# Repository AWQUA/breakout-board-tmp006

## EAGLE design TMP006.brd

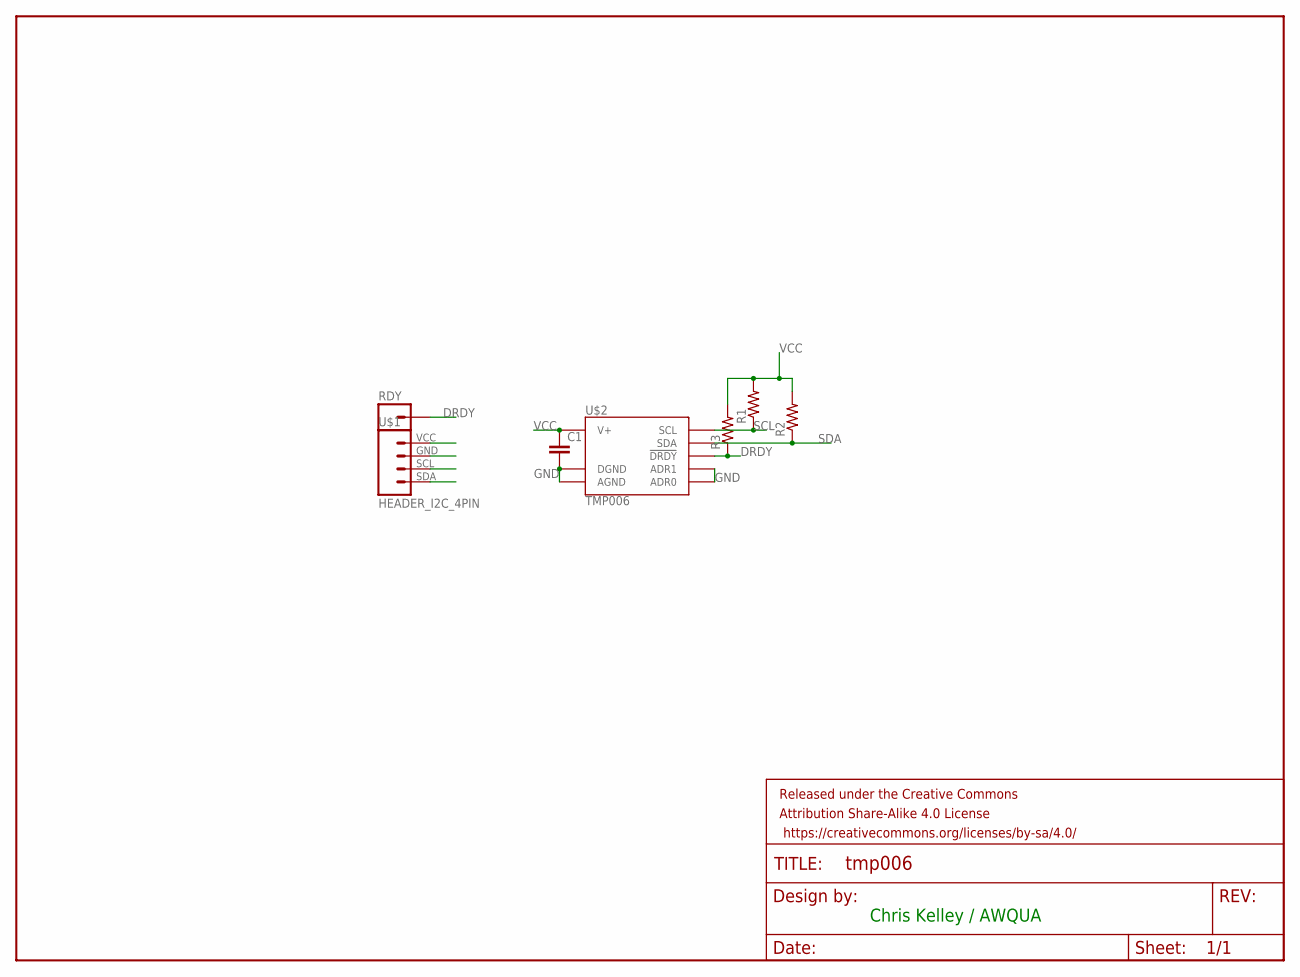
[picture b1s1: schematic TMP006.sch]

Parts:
C1: CAP0603-CAP; 0603-CAP
FRAME1: FRAME-LETTER; CREATIVE_COMMONS
R1, R2, R3: RESISTOR0603-RES; 0603-RES
RDY: M01PTH; 1X01
U$1: HEADER_I2C_4PIN
U$2: TMP006

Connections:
DRDY: R3.1, RDY.1, U$2.DRDY (!DRDY)
GND: C1.2, U$1.GND, U$2.ADR0, U$2.ADR1, U$2.AGND, U$2.DGND
SCL: R1.1, U$1.SCL, U$2.SCL
SDA: R2.1, U$1.SDA, U$2.SDA
VCC: C1.1, R1.2, R2.2, R3.2, U$1.VCC, U$2.VCC (V+)

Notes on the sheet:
Chris Kelley / AWQUA

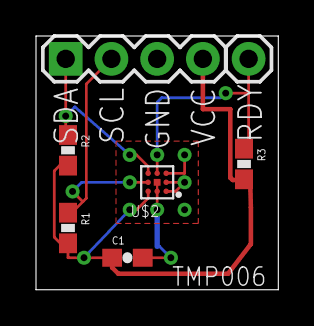
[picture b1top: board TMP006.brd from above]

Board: 2 copper layers, 13.5 x 14.1 mm, 8 parts (0 on the bottom side), 5 nets.

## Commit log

2017-03-09 board added

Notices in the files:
parts and their libraries:
SparkFun-Aesthetics: Licensing: Creative Commons ShareAlike 4.0 International - https://creativecommons.org/licenses/by-sa/4.0
SparkFun-Aesthetics: Released under the Creative Commons Attribution Share-Alike 4.0 License
SparkFun-Aesthetics: https://creativecommons.org/licenses/by-sa/4.0
